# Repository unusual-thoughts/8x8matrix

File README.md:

Backpack for 8x8 RGB LED matrix
==============================

This is a simple breakout board for 8x8 RGB matrices like the [GTM2088ARGB](http://www.ebay.com/itm/5mm-8x8-Matrix-RGB-LED-Common-Anode-Full-Colour-60-60mm-/370699782315)  
It uses a [TLC5947](http://www.ti.com/product/tlc5947) that provides 24 12 bit current sink PWM channels, and a 74HC138 3 to 8 line decoder followed by P-channel MOSFETs to drive the rows.  

The needed Eagle libraries are in `eagle-lbr/`  
The whole thing fits on a single layer PCB.  
The matrix is controlled through the 9-pin header with this pinout:

Pin number	| Label	| Description
----------	| -----	| -----------
1			| A2	| row higher bit
2			| A1	| row middle bit
3			| A0	| row lower bit
4			| SIN	| TLC data (24x12 bit = 36 bytes)
5			| SCLK	| TLC clock
6			| BLANK	| TLC blank columns and reset PWM timer
7			| GND	| Ground
8			| VCC	| +5V
9			| XLAT	| TLC latch data

To get everything to fit on a single sided board, I had to make weird column and row assignments:

A0	| A1	| A2	| Row Number
--- | ---	| ---	| ----------
0	| 0		| 0		| 2
0	| 0		| 1		| 1
0	| 1		| 0		| 0
0	| 1		| 1		| 7
1	| 0		| 0		| 4
1	| 0		| 1		| 5
1	| 1		| 0		| 6
1	| 1		| 1		| 3

TLC channel	| Columns
----------  | ------
0-7			| Red 0-7
8-15		| Blue 0-7
16-23		| Green 7-0 (inverted order)

The `arduino-lbr/` directory contatins a modified version of the Tlc5940 library by Alex Leone, named Tlc5947. Like its counterpart, it can use arduino hardware spi to speed things up to an acceptable refresh rate. The basic bitbang code flickers quite a bit, even with direct port manipulation.

The `arduino/` directory contains a demo arduino sketch using that library.

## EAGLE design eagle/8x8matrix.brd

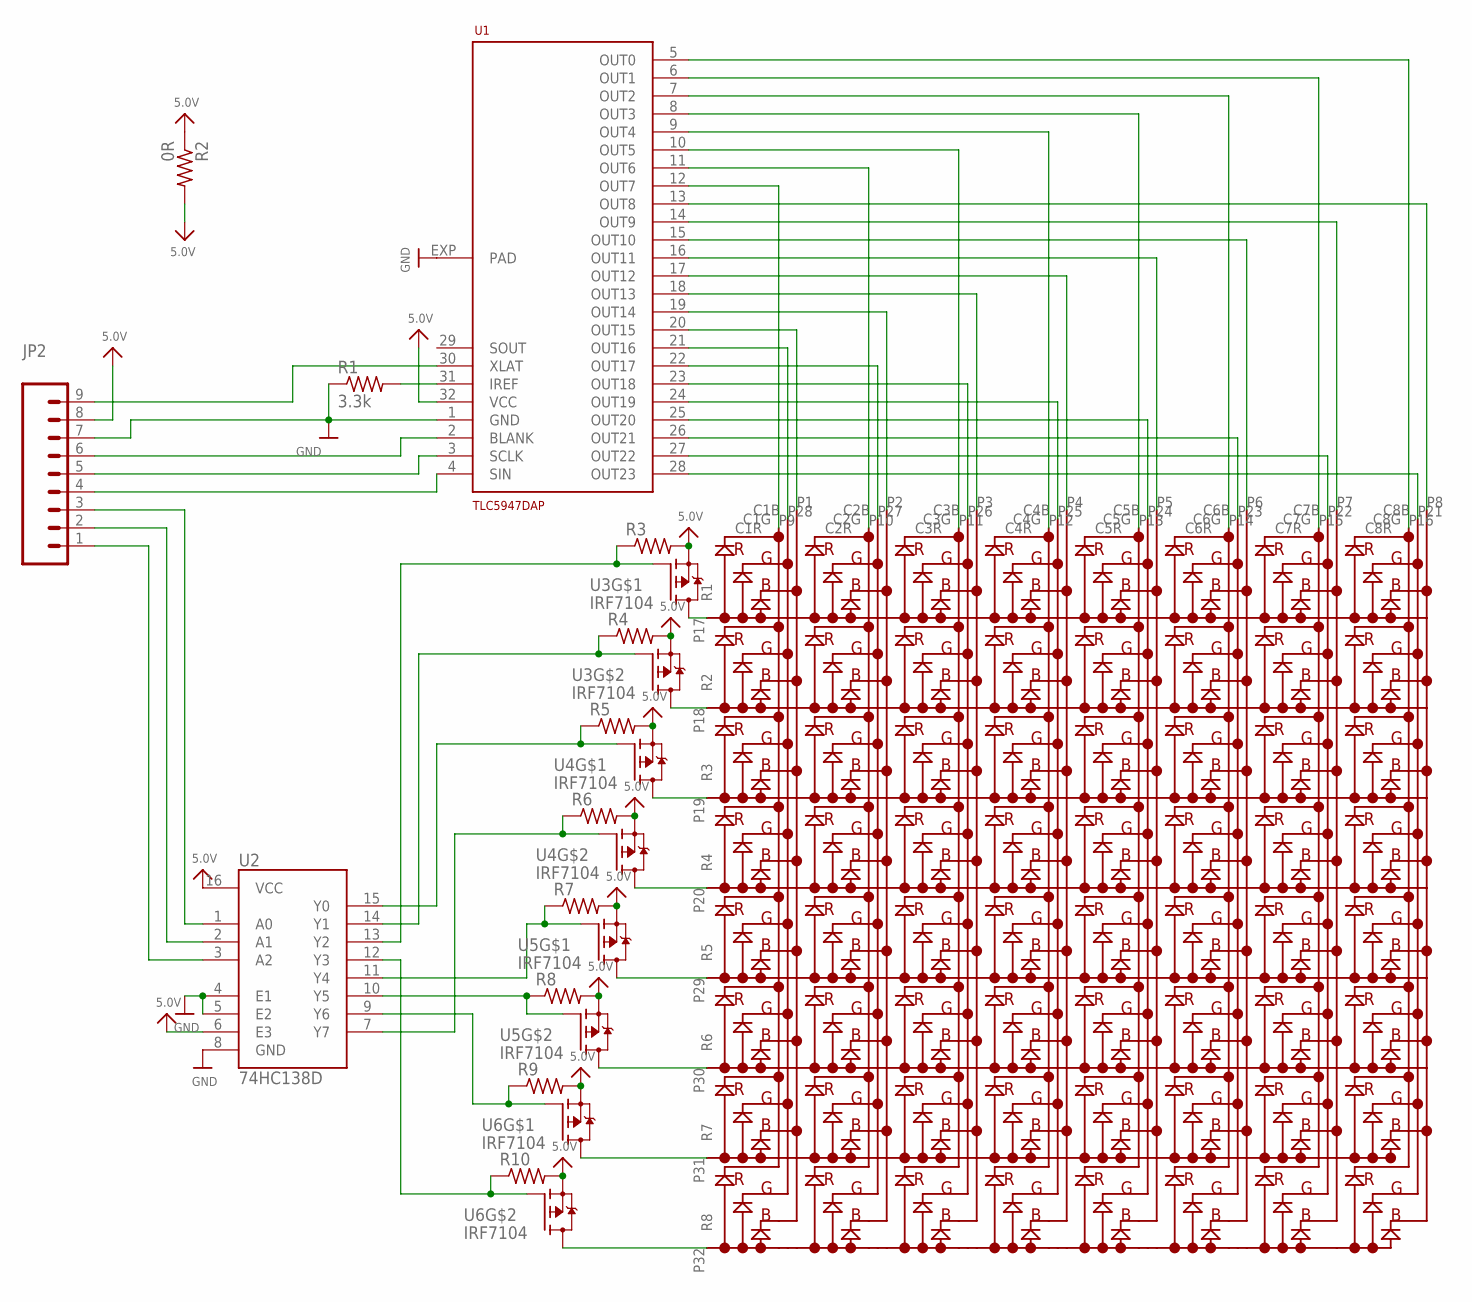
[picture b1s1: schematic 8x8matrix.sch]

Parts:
JP2: M09; 1X09
R1: 3.3k; R0805
R2: 0R; M1206
R3, R4, R5, R6, R7, R8, R9, R10: R-US_R0805; R0805
U1: TLC5947DAP; HTSSOP32DAP
U2: 74HC138D; SO-16
U3, U4, U5, U6: IRF7104; SOIC8
U$1: GTM2088ARGB; 8X8MATRIX

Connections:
5.0V: JP2.8, R2.1, R2.2, R3.2, R4.2, R5.2, R6.2, R7.2, R8.2, R9.2, R10.2, U1.32 (VCC), U2.6 (E3), U2.16 (VCC), U3.1 (S), U3.3 (S), U4.1 (S), U4.3 (S), U5.1 (S), U5.3 (S), U6.1 (S), U6.3 (S)
A0: JP2.3, U2.1 (A0)
A1: JP2.2, U2.2 (A1)
A2: JP2.1, U2.3 (A2)
BLANK: JP2.6, U1.2 (BLANK)
GND: JP2.7, R1.1, U1.1 (GND), U1.EXP (PAD), U2.4 (E1), U2.5 (E2), U2.8 (GND)
unnamed: U1.5 (OUT0), U$1.P16 (C8R)
unnamed: U1.6 (OUT1), U$1.P15 (C7R)
unnamed: U1.7 (OUT2), U$1.P14 (C6R)
unnamed: U1.8 (OUT3), U$1.P13 (C5R)
unnamed: U1.9 (OUT4), U$1.P12 (C4R)
unnamed: U1.10 (OUT5), U$1.P11 (C3R)
unnamed: U1.11 (OUT6), U$1.P10 (C2R)
unnamed: U1.12 (OUT7), U$1.P9 (C1R)
unnamed: U1.13 (OUT8), U$1.P8 (C8B)
unnamed: U1.14 (OUT9), U$1.P7 (C7B)
unnamed: U1.15 (OUT10), U$1.P6 (C6B)
unnamed: U1.16 (OUT11), U$1.P5 (C5B)
unnamed: U1.17 (OUT12), U$1.P4 (C4B)
unnamed: U1.18 (OUT13), U$1.P3 (C3B)
unnamed: U1.19 (OUT14), U$1.P2 (C2B)
unnamed: U1.20 (OUT15), U$1.P1 (C1B)
unnamed: U1.21 (OUT16), U$1.P28 (C1G)
unnamed: U1.22 (OUT17), U$1.P27 (C2G)
unnamed: U1.23 (OUT18), U$1.P26 (C3G)
unnamed: U1.24 (OUT19), U$1.P25 (C4G)
unnamed: U1.25 (OUT20), U$1.P24 (C5G)
unnamed: U1.26 (OUT21), U$1.P23 (C6G)
unnamed: U1.27 (OUT22), U$1.P22 (C7G)
unnamed: U1.28 (OUT23), U$1.P21 (C8G)
unnamed: R1.2, U1.31 (IREF)
unnamed: U4.7 (D), U4.8 (D), U$1.P19 (R3)
unnamed: U3.5 (D), U3.6 (D), U$1.P18 (R2)
unnamed: U3.7 (D), U3.8 (D), U$1.P17 (R1)
unnamed: U5.7 (D), U5.8 (D), U$1.P29 (R5)
unnamed: U6.7 (D), U6.8 (D), U$1.P31 (R7)
unnamed: U4.5 (D), U4.6 (D), U$1.P20 (R4)
unnamed: U5.5 (D), U5.6 (D), U$1.P30 (R6)
unnamed: U6.5 (D), U6.6 (D), U$1.P32 (R8)
SCLK: JP2.5, U1.3 (SCLK)
SIN: JP2.4, U1.4 (SIN)
XLAT: JP2.9, U1.30 (XLAT)
Y0: R5.1, U2.15 (Y0), U4.2 (G)
Y1: R4.1, U2.14 (Y1), U3.4 (G)
Y2: R3.1, U2.13 (Y2), U3.2 (G)
Y3: R10.1, U2.12 (Y3), U6.4 (G)
Y4: R7.1, U2.11 (Y4), U5.2 (G)
Y5: R8.1, U2.10 (Y5), U5.4 (G)
Y6: R9.1, U2.9 (Y6), U6.2 (G)
Y7: R6.1, U2.7 (Y7), U4.4 (G)

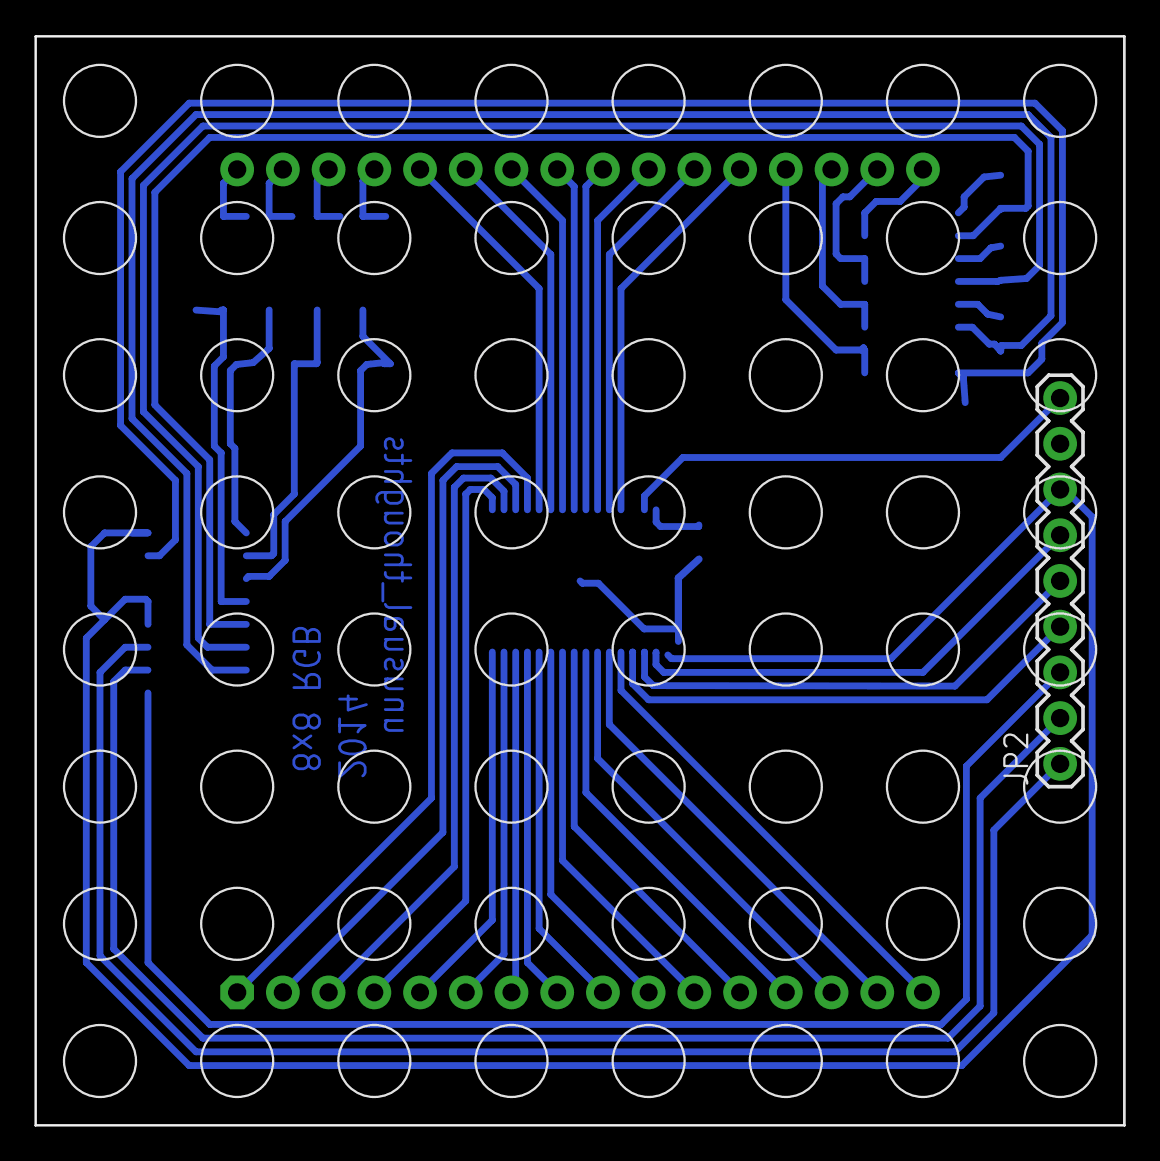
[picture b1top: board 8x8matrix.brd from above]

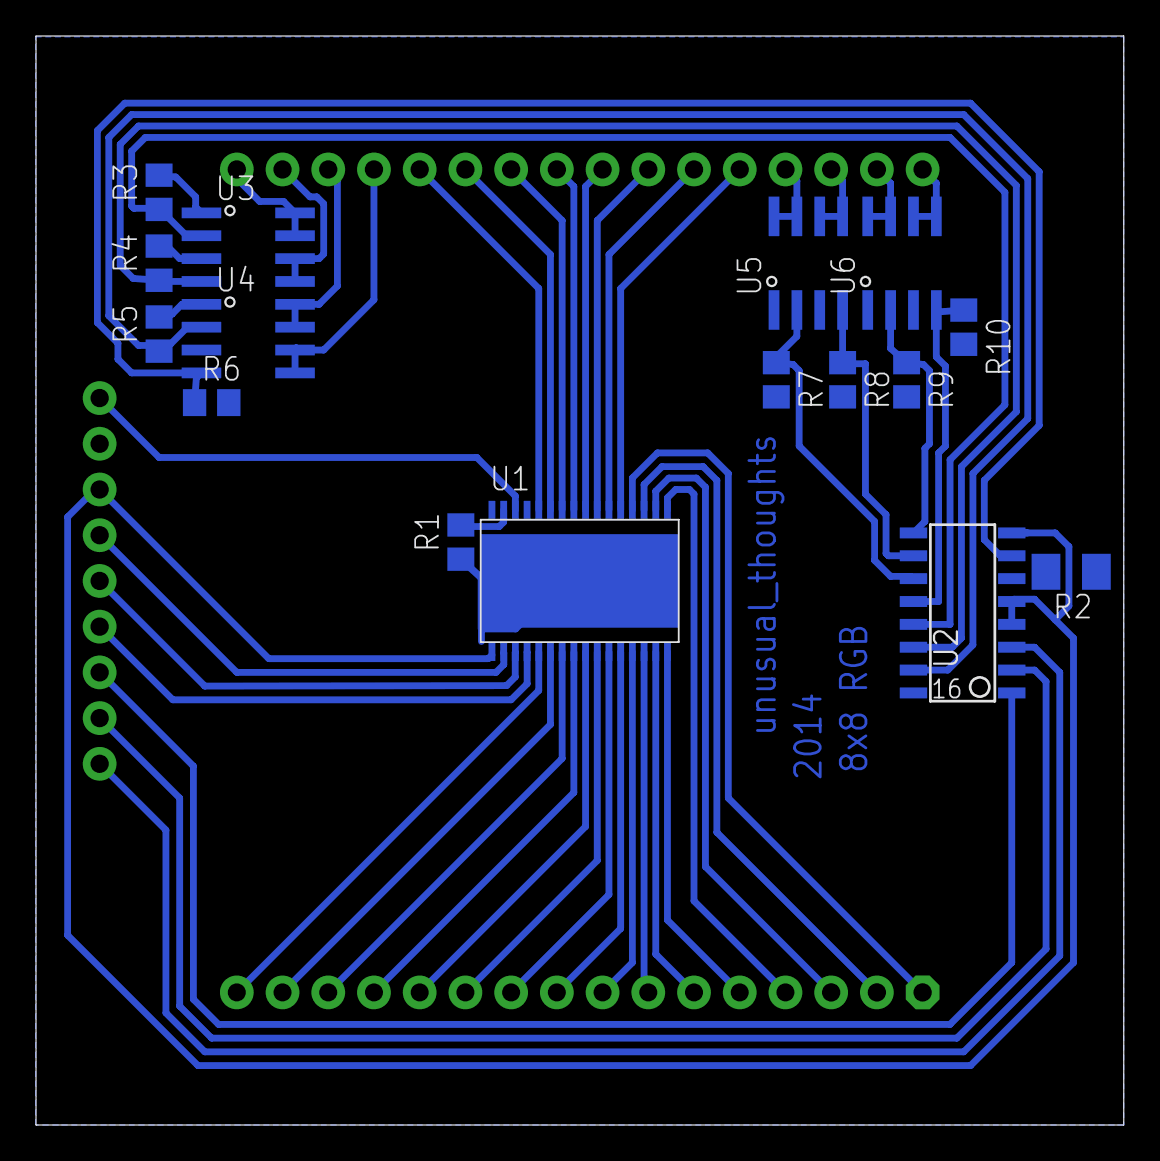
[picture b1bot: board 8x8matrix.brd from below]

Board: 2 copper layers, 60.4 x 60.5 mm, 18 parts (16 on the bottom side), 50 nets.

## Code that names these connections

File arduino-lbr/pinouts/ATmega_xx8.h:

/*  Copyright (c) 2009 by Alex Leone <acleone ~AT~ gmail.com>

    This file is part of the Arduino TLC5940 Library.

    The Arduino TLC5940 Library is free software: you can redistribute it
    and/or modify it under the terms of the GNU General Public License as
    published by the Free Software Foundation, either version 3 of the
    License, or (at your option) any later version.

    The Arduino TLC5940 Library is distributed in the hope that it will be
    useful, but WITHOUT ANY WARRANTY; without even the implied warranty of
    MERCHANTABILITY or FITNESS FOR A PARTICULAR PURPOSE.  See the
    GNU General Public License for more details.

    You should have received a copy of the GNU General Public License
    along with The Arduino TLC5940 Library.  If not, see
    <http://www.gnu.org/licenses/>. */

#ifndef TLC_ATMEGA_XX8_H
#define TLC_ATMEGA_XX8_H

/** \file
    SPI and timer pins for the ATmega168/48/88.  Don't edit these.  All
    changeable pins are defined in tlc_config.h */


/** SIN (Arduino digital pin 7) -> SIN (TLC pin 26) */
#define DEFAULT_BB_SIN_PIN      PD7
#define DEFAULT_BB_SIN_PORT     PORTD
#define DEFAULT_BB_SIN_DDR      DDRD
/** SCLK (Arduino digital pin 4) -> SCLK (TLC pin 25) */
#define DEFAULT_BB_SCLK_PIN     PD4
#define DEFAULT_BB_SCLK_PORT    PORTD
#define DEFAULT_BB_SCLK_DDR     DDRD

/** MOSI (Arduino digital pin 11) -> SIN (TLC pin 26) */
#define TLC_MOSI_PIN     PB3
#define TLC_MOSI_PORT    PORTB
#define TLC_MOSI_DDR     DDRB

/** SCK (Arduino digital pin 13) -> SCLK (TLC pin 25) */
#define TLC_SCK_PIN      PB5
#define TLC_SCK_PORT     PORTB
#define TLC_SCK_DDR      DDRB

/** SS will be set to output as to not interfere with SPI master operation.
    If you have changed the pin-outs and the library doesn't seem to work
    or works intermittently, make sure this pin is set correctly.  This pin
    will not be used by the library other than setting its direction to
    output. */
#define TLC_SS_PIN       PB2
#define TLC_SS_DDR       DDRB

/** OC1A (Arduino digital pin 9) -> XLAT (TLC pin 24) */
#define XLAT_PIN     PB1
#define XLAT_PORT    PORTB
#define XLAT_DDR     DDRB

/** OC1B (Arduino digital pin 10) -> BLANK (TLC pin 23) */
#define BLANK_PIN    PB2
#define BLANK_PORT   PORTB
#define BLANK_DDR    DDRB

/** OC2B (Arduino digital pin 3) -> GSCLK (TLC pin 18) */
#define GSCLK_PIN    PD3
#define GSCLK_PORT   PORTD
#define GSCLK_DDR    DDRD

#endif

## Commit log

2017-11-06 fix compilation errors
2017-11-08 update eagle schematic
2017-11-08 add schematic images
2017-11-08 add schematic to readme

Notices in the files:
parts and their libraries:
SparkFun-Connectors: Licensing: Creative Commons ShareAlike 4.0 International - https://creativecommons.org/licenses/by-sa/4.0
microbuilder: This work is placed in the public domain, and may be freely used for commercial and non-commercial work with the following conditions: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
